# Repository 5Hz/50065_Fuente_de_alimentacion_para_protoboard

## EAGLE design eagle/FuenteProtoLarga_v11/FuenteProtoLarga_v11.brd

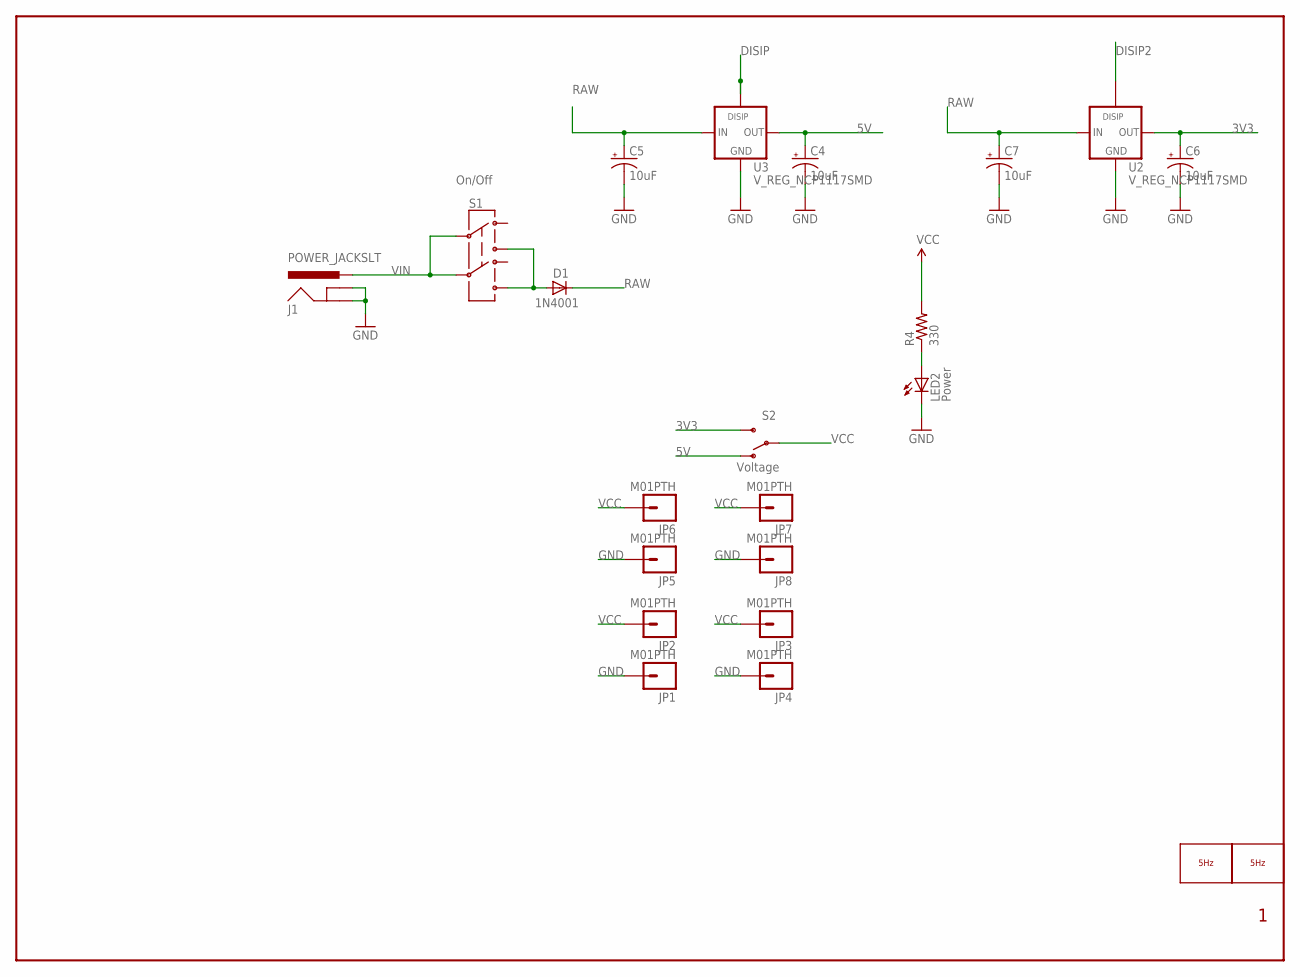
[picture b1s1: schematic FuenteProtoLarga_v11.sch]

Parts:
C4, C5, C6, C7: 10uF; EIA3216
D1: 1N4001; SMA-DIODE
J1: POWER_JACKSLT; POWER_JACK_SLOT
JP1, JP2, JP3, JP4, JP5, JP6, JP7, JP8: M01PTH; 1X01
LED2: Power; LED-0603
LOGO1: LOGO_5HZ_H_10MM; 5HZ_LOGO_H_10MM
LOGO2: LOGO_5HZ_H_COOPER_15MM; 5HZ_LOGO_H_COOPER_15MM
R4: 330; 0603-RES
S1: On/Off; AYZ0202
S2: Voltage; AYZ0202
U2, U3: V_REG_NCP1117SMD; SOT223

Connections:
3V3: C6.A (+), S2.3 (S), U2.2 (OUT)
5V: C4.A (+), S2.1 (O), U3.2 (OUT)
DISIP: U3.4
DISIP2: U2.4
GND: C4.C (-), C5.C (-), C6.C (-), C7.C (-), J1.GND@1 (GNDBREAK), J1.GND@2 (GND), JP1.1, JP4.1, JP5.1, JP8.1, LED2.C, U2.1 (GND), U3.1 (GND)
unnamed: D1.A, S1.1 (3), S1.4 (6)
unnamed: LED2.A, R4.1
RAW: C5.A (+), C7.A (+), D1.C, U2.3 (IN), U3.3 (IN)
VCC: JP2.1, JP3.1, JP6.1, JP7.1, R4.2, S2.2
VIN: J1.PWR, S1.2, S1.5

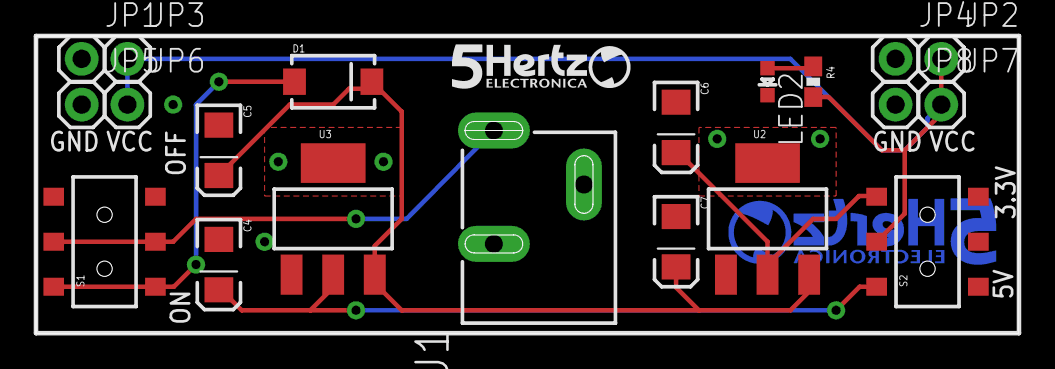
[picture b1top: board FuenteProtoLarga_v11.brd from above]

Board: 2 copper layers, 54.6 x 16.5 mm, 22 parts (1 on the bottom side), 8 nets.

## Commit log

2014-01-13 creación
